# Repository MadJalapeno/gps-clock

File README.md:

## Note

This is still a work in progress. 

Things that work:

- GPS module
- Screen

Things that may work, but have not been tested:

- Stepper drivers

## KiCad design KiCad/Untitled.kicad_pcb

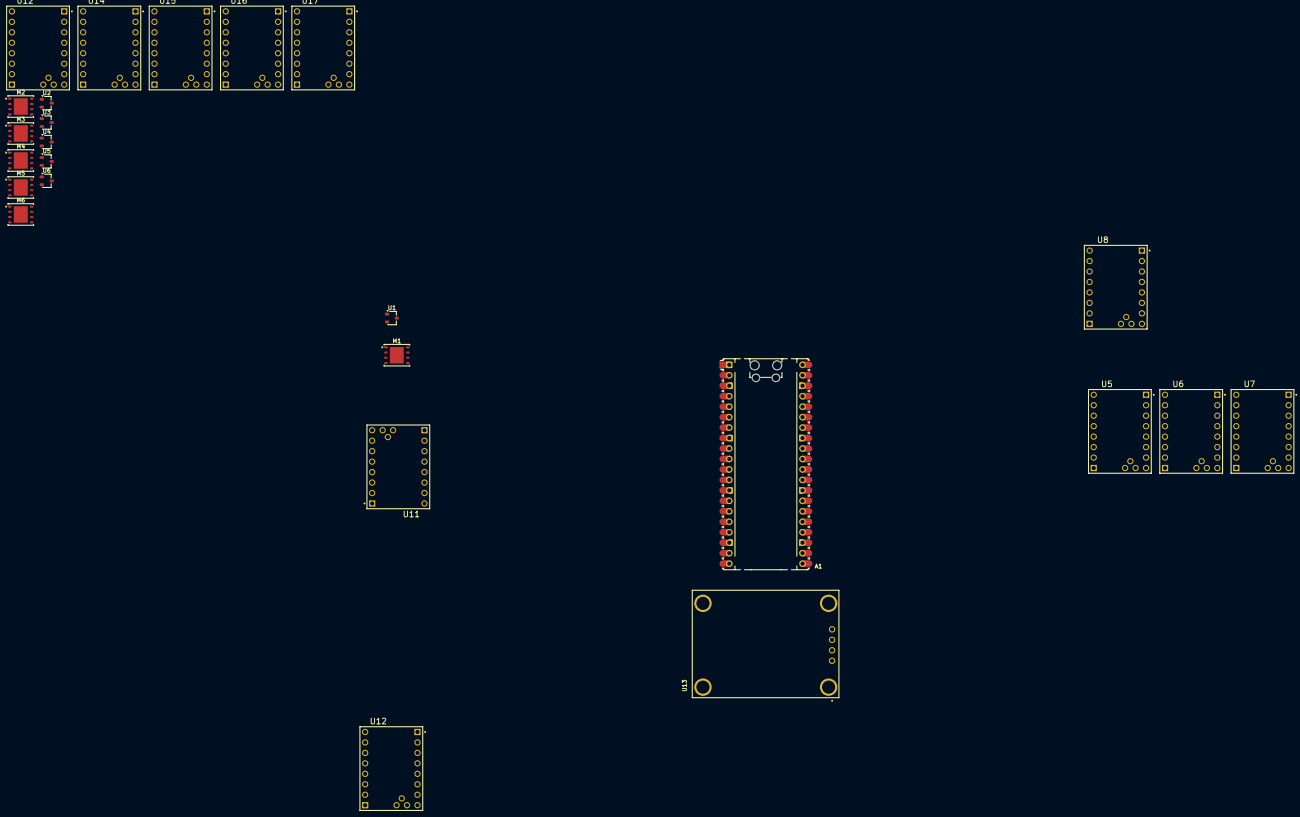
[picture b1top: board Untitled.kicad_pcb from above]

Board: 2 copper layers, 25 parts (0 on the bottom side), 36 nets, no tracks yet.

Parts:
A1: RaspberryPi_Pico; RaspberryPi_Pico_Common_Unspecified
M1, M2, M3, M4, M5, M6: Stepper_Motor_bipolar; WSON-8-1EP_6x5mm_P1.27mm_EP3.4x4mm
U1, U2, U3, U4, U5, U6: A1104xLH; SOT-23W
U5#2, U6#2, U7, U8, U11, U12, U12#2, U14, U15, U16, U17: TMC2208_SILENTSTEPSTICK; MODULE_TMC2208_SILENTSTEPSTICK
U13: ZC323200; XCVR_ZC323200

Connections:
/+24V: U11.JP2_1 (VM), U12.JP2_1 (VM), U14.JP2_1 (VM), U15.JP2_1 (VM), U16.JP2_1 (VM), U17.JP2_1 (VM)
/<NO NET>: A1.36 (3V3), U1.1 (V_{CC}), U2.1 (V_{CC}), U3.1 (V_{CC}), U4.1 (V_{CC}), U5.1 (V_{CC}), U6.1 (V_{CC}), U11.JP2_7 (VIO), U12.JP2_7 (VIO), U13.1 (VCC), U14.JP2_7 (VIO), U15.JP2_7 (VIO), U16.JP2_7 (VIO), U17.JP2_7 (VIO)
/GPS - RX: A1.2 (GPIO1), U13.2 (RX)
/GPS - TX: A1.1 (GPIO0), U13.3 (TX)
/SECONDS_ONE_DIR: A1.19 (GPIO14), U11.JP1_1 (DIR)
/SECONDS_ONE_HOME: A1.5 (GPIO3), U1.2 (V_{OUT})
/SECONDS_ONE_STEP: A1.4 (GPIO2), U11.JP1_2 (STEP)
/SECONDS_TENS_DIR: A1.20 (GPIO15), U12.JP1_1 (DIR)
/SECONDS_TENS_HOME: A1.7 (GPIO5), U2.2 (V_{OUT})
/SECONDS_TENS_STEP: A1.6 (GPIO4), U12.JP1_2 (STEP)
GND: A1.3 (GND), A1.8 (GND), A1.13 (GND), A1.18 (GND), A1.23 (GND), A1.28 (GND), A1.38 (GND), U1.3 (GND), U2.3 (GND), U3.3 (GND), U4.3 (GND), U5.3 (GND), U5#2.JP2_2 (GND), U5#2.JP2_8 (GND), U6.3 (GND), U6#2.JP2_2 (GND), U6#2.JP2_8 (GND), U7.JP2_2 (GND), U7.JP2_8 (GND), U8.JP2_2 (GND), U8.JP2_8 (GND), U11.JP2_2 (GND), U11.JP2_8 (GND), U12.JP2_2 (GND), U12.JP2_8 (GND), U12#2.JP2_2 (GND), U12#2.JP2_8 (GND), U13.4 (GND), U14.JP2_2 (GND), U14.JP2_8 (GND), U15.JP2_2 (GND), U15.JP2_8 (GND), U16.JP2_2 (GND), U16.JP2_8 (GND), U17.JP2_2 (GND), U17.JP2_8 (GND)
unnamed: M1.2 (-_2), U11.JP2_4 (OA1)
unnamed: M2.2 (-_2), U12.JP2_4 (OA1)
unnamed: M3.2 (-_2), U14.JP2_4 (OA1)
unnamed: M4.2 (-_2), U15.JP2_4 (OA1)
unnamed: M5.2 (-_2), U16.JP2_4 (OA1)
unnamed: M6.2 (-_2), U17.JP2_4 (OA1)
unnamed: M1.1, U11.JP2_3 (OA2)
unnamed: M1.3, U11.JP2_5 (OB1)
unnamed: M1.4, U11.JP2_6 (OB2)
unnamed: M2.1, U12.JP2_3 (OA2)
unnamed: M2.3, U12.JP2_5 (OB1)
unnamed: M2.4, U12.JP2_6 (OB2)
unnamed: U13.SH1 (SHIELD), U13.SH2 (SHIELD), U13.SH3 (SHIELD), U13.SH4 (SHIELD)
unnamed: M3.1, U14.JP2_3 (OA2)
unnamed: M3.3, U14.JP2_5 (OB1)
unnamed: M3.4, U14.JP2_6 (OB2)
unnamed: M4.1, U15.JP2_3 (OA2)
unnamed: M4.3, U15.JP2_5 (OB1)
unnamed: M4.4, U15.JP2_6 (OB2)
unnamed: M5.1, U16.JP2_3 (OA2)
unnamed: M5.3, U16.JP2_5 (OB1)
unnamed: M5.4, U16.JP2_6 (OB2)
unnamed: M6.1, U17.JP2_3 (OA2)
unnamed: M6.3, U17.JP2_5 (OB1)
unnamed: M6.4, U17.JP2_6 (OB2)

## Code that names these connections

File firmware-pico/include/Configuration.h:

#ifndef CONFIGURATION_H
#define CONFIGURATION_H

// ============================================================================
// COMMUNICATION SETTINGS
// ============================================================================
#define SERIAL_BAUD_RATE        115200  // Console serial port baud rate
#define GPS_BAUD_RATE           9600    // GPS serial port baud rate

// ============================================================================
// HARDWARE CONFIGURATION
// ============================================================================

// ============================================================================
// TFT Display (ST7735) Pin Assignments - SPI Interface
// ============================================================================
// Display Module Wiring:
//   Display GND   → Pico GND
//   Display VCC   → Pico 3.3V
//   Display SCL   → Pico GPIO 18 (SPI Clock)
//   Display SDA   → Pico GPIO 19 (SPI Data/MOSI)
//   Display RES   → Pico GPIO 21 (Reset)
//   Display DC    → Pico GPIO 20 (Data/Command)
//   Display CS    → Pico GPIO 17 (Chip Select)
//   Display BLK   → Pico 3.3V (Backlight - always on)
// ============================================================================
#define TFT_MISO_PIN            16       // Hardware SPI MISO (not used - write-only)
#define TFT_CS_PIN              17       // TFT chip select
#define TFT_SCK_PIN             18       // Hardware SPI SCK (Display SCL)
#define TFT_MOSI_PIN            19       // Hardware SPI MOSI (Display SDA)
#define TFT_DC_PIN              20       // TFT data/command
#define TFT_RST_PIN             21       // TFT reset

// GPS Serial Pin Assignments
#define GPS_TX_PIN              0
#define GPS_RX_PIN              1

// Motor 0 - Hours Tens Place
#define HOURS_TENS_STEP_PIN     12
#define HOURS_TENS_DIR_PIN      14      // Shared with Motor 1
#define HOURS_TENS_HOME_PIN     13      // Hall sensor input (A1104)

// Motor 1 - Hours Ones Place
#define HOURS_ONES_STEP_PIN     10
#define HOURS_ONES_DIR_PIN      14      // Shared with Motor 0
#define HOURS_ONES_HOME_PIN     11      // Hall sensor input (A1104)

// Motor 2 - Minutes Tens Place
#define MINUTES_TENS_STEP_PIN   8
#define MINUTES_TENS_DIR_PIN    15      // Shared with Motor 3
#define MINUTES_TENS_HOME_PIN   9       // Hall sensor input (A1104)

// Motor 3 - Minutes Ones Place
#define MINUTES_ONES_STEP_PIN   6
#define MINUTES_ONES_DIR_PIN    15      // Shared with Motor 2
#define MINUTES_ONES_HOME_PIN   7       // Hall sensor input (A1104)

// Motor 4 - Seconds Tens Place
#define SECONDS_TENS_STEP_PIN   4
#define SECONDS_TENS_DIR_PIN    22      // Shared with Motor 5
#define SECONDS_TENS_HOME_PIN   5       // Hall sensor input (A1104)

// Motor 5 - Seconds Ones Place
#define SECONDS_ONES_STEP_PIN   2
#define SECONDS_ONES_DIR_PIN    22      // Shared with Motor 4
#define SECONDS_ONES_HOME_PIN   3       // Hall sensor input (A1104)

// ============================================================================
// HALL EFFECT SENSOR CONFIGURATION (A1104 Sensors)
// ============================================================================
// Each motor has an A1104 Hall effect sensor for home position detection
// Sensors output 0-5V analog signal based on magnetic field strength
// Can be used with Pico ADC or comparator for home detection
#define HALL_SENSOR_0           13      // Motor 0 (Hours Tens) - also GPIO13
#define HALL_SENSOR_1           11      // Motor 1 (Hours Ones) - also GPIO11
#define HALL_SENSOR_2           9       // Motor 2 (Minutes Tens) - also GPIO9
#define HALL_SENSOR_3           7       // Motor 3 (Minutes Ones) - also GPIO7
#define HALL_SENSOR_4           5       // Motor 4 (Seconds Tens) - also GPIO5
#define HALL_SENSOR_5           3       // Motor 5 (Seconds Ones) - also GPIO3

// Hall sensor detection threshold (for digital input)
// When magnet passes sensor, output goes low (~0.2V) / high (~2.5V)
#define HALL_DETECTION_THRESHOLD_LOW    0.5     // Volts (if using ADC)
#define HALL_DETECTION_THRESHOLD_HIGH   2.0     // Volts (if using ADC)

// Hall sensor: 5V supply and GND from motor power board
// Output signal filtered with 100nF capacitor

// Control Pins
#define ENABLE_PIN              22      // Active low - enables all stepper motors
#define LED_PIN                 LED_BUILTIN  // Use Pico built-in LED (GPIO25)
#define DEBUG_PIN               28      // Debug timing pin for performance measurement
#define TIMEZONE_BUTTON_PIN     26      // Timezone offset button (active low with pull-up)
#define H24_BUTTON_PIN          27      // 24H/12H format toggle button (active low with pull-up)

// Button Debounce Configuration
#define BUTTON_DEBOUNCE_MS      50     // Debounce time in milliseconds
#define BUTTON_LONG_PRESS_MS    2000   // Long press time in milliseconds

// Watchdog Timer Configuration
#define WATCHDOG_TIMEOUT_MS     4000    // Watchdog timer timeout in milliseconds

// ============================================================================
// POWER SUPPLY CONFIGURATION
// ============================================================================
#define MOTOR_SUPPLY_VOLTAGE    24      // Motor supply voltage (24V direct from barrel jack)
#define LOGIC_SUPPLY_VOLTAGE    5       // Logic supply voltage (from MP6524 buck converter)
#define BUCK_CONVERTER_INPUT    24      // MP6524: 24V input -> 5V output
#define BUCK_CONVERTER_OUTPUT   5

// ============================================================================
// MOTOR CONFIGURATION - NEMA 11, 24V, 200 steps/rev
// ============================================================================
#define MOTOR_TYPE              "NEMA11_24V"
#define MOTOR_STEPS_PER_REV     200     // NEMA 11 stepper: 200 steps per revolution
#define MOTOR_VOLTAGE           24      // Motor rated for 24V
#define MOTOR_CURRENT_MAX       0.67    // Motor max current: 0.67A per phase

// Microstepping configuration (TMC2208 driver)
#define MICROSTEPS              8       // 8 microsteps per full step
#define STEPS_PER_FULL_STEP     200     // Full steps per revolution
#define STEPS_PER_MICROSTEP     (MOTOR_STEPS_PER_REV * MICROSTEPS)  // 1600 microsteps per rev

// Display positions (0-9 for each digit)
#define NUM_POSITIONS           10      // Each digit shows 0-9
#define STEPS_PER_POSITION      (STEPS_PER_MICROSTEP / NUM_POSITIONS)  // 160 microsteps per position

// Motor control speeds
#define MOTOR_HOMING_SPEED      2500    // Steps per second during homing
#define MOTOR_MAX_SPEED         5000    // Steps per second
#define MOTOR_ACCELERATION      10000   // Steps per second²

// Per-motor homing offset (steps to advance after Hall sensor triggers)
// Calibrated for mechanical lever position on each digit wheel
#define HOMING_OFFSET_STEPS_HOURS_TENS      (175 + STEPS_PER_POSITION * 10)
#define HOMING_OFFSET_STEPS_HOURS_ONES      (167 + STEPS_PER_POSITION * 10)
#define HOMING_OFFSET_STEPS_MINUTES_TENS    (175 + STEPS_PER_POSITION * 10)
#define HOMING_OFFSET_STEPS_MINUTES_ONES    (170 + STEPS_PER_POSITION * 10)
#define HOMING_OFFSET_STEPS_SECONDS_TENS    (175 + STEPS_PER_POSITION * 10)
#define HOMING_OFFSET_STEPS_SECONDS_ONES    (169 + STEPS_PER_POSITION * 10)

// ============================================================================
// STEPPER DRIVER CONFIGURATION - TMC2208-24V
// ============================================================================
#define STEPPER_DRIVER_MODEL    "TMC2208"
#define STEPPER_DRIVER_VOLTAGE  24      // TMC2208-24V rated for 24V
#define STEPPER_RMS_CURRENT     0.67    // RMS current limit matches NEMA 11 rating
// TMC2208 pins: STEP, DIR, ENA (shared enable on GPIO22)
// Motors 0-1 share DIR on GPIO14
// Motors 2-3 share DIR on GPIO15
// Motors 4-5 share DIR on GPIO22 (also used as ENABLE)

#endif // CONFIGURATION_H

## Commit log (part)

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2026-02-22 Use the fifo instead of idling the other core when updating motors
2026-02-26 Allow per-motor direction configuration with multiple direction pins.
2026-02-27 Use separate buttons for time zone and 24 hour format
2026-02-27 Motors don't actually need to be reversed because the physical motors are switched. Slow things down for bigger wheels.
2026-02-28 Reverse pin assignments and slow everything down.
2026-03-01 Only try to commit the EEPROM after a config change when all motors are stopped, to avoid missed steps due to interrupting motion.
2026-03-01 Raise the operating speed, now that we're no longer hiccupping when changing settings.
2026-03-07 Fix waiting for GPS message
